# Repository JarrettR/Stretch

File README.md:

Note: Due to the constantly moving target of the KiCad file format, and also more importantly, the [new IPC plugin system](https://dev-docs.kicad.org/en/apis-and-binding/ipc-api/), this plugin hasn't been fully tested in 9, and support will be extremely limited. Some people have seen success in version 9, and I'm still happy to accept PRs, but I'm unlikely to be diving into it myself.

# Stretch

Allow your PCBs to _stretch_!

## The Process

In KiCad:

In Inkscape:

Modify:

Back to KiCad:

## Why?

This was written to address some frustrations with other "artistic" PCB workflows.
KiCad and other traditional ECAD software has poor support for curved lines, importing and processing of images/drawings, and many other features that can be expected in proper vector software.

Tools intended to bridge the gap are also lacking. [PCBmodE](https://github.com/boldport/pcbmode) is the probably the best tool out there from a pure PCB art standpoint, and it is excellent, but there is no schematic tool. And with that, no ability to handle extremely complex, functional PCBs.

KiCad has a tool to export to SVG. SVG-To-Shenzen is a tool to convert SVG files into KiCad files. Both of these are single-direction tools.

Stretch goes both ways. Much as the ideal schematic->PCB capture workflow does not exist, the PCB layout aspect must go hand-in-hand with the art aspect.

Users can start by drawing a schematic and laying out a PCB, then bring it into Inkscape to arrange a thousand LEDs into a flower arrangement, then bring it back into KiCad to lay out traces, back into Inkscape to curve the traces, back into KiCad to change their microcontroller and few pin assignments, back into Inkscape to draw out some silkscreem patterns, back into KiCad to run DRC, and so on.
The workflow is intended to be seamless and painless to go back and forth.

## Installation

- Copy this main Stretch folder into your KiCad plugin folder at `Tools->External Plugins...->Open Plugin Directory`
- Ensure the BeautifulSoup4 library is installed (e.g. run `pip install bs4` in a system command line, see Troubleshooting below for details)
- Open up a PCB and then in Pcbnew, got to `Tools->External Plugins...->Refresh Plugins`
- This has been tested on KiCad 6 and later. For a KiCad 5 legacy version, check the releases.

### Troubleshooting

If the buttons do not show up on the toolbar, the plugin may be installed but not loading successfully. The most common cause is a missing `bs4` library, which is required to run Stretch. Firstly, check to see if there are any error messages by opening up the Scripting Console from `Tools->Scripting Console` and in the "Shell" section at the top, click after the `>>>` prompt (you may have to scroll down) and type `from com_github_jarrettr_stretch import Stretch`. If you get the `>>>` prompt again without any other text, the plugin is loading correctly. Otherwise, there will be an error message: pay attention to the last line.

If it says `No module named 'bs4'`, BeatifulSoup is not installed. If you have installed it but are still getting this error, try using `pip3` instead of `pip`, or install the library with your package manager (e.g. `apt install python3-bs4`).

It's also possible to have multiple installations of Python, in which case you need to run the `pip` command from the correct installation, which can be difficult to determine. This is often the case on MacOS, where KiCad uses its own installation of Python than the system installation. To find out where the Python that KiCad is using is, go back to the `>>>` prompt above and type:
```
import sys
print(sys.base_exec_prefix)
```
This will print out a path (e.g. `/usr` or `/Applications/KiCad/KiCad.app/Contents/Frameworks/Python.framework/Versions/Current`). You should be able to add `/bin/pip` (or `pip3`) to this path and run e.g. `/Applications/KiCad/KiCad.app/Contents/Frameworks/Python.framework/Versions/Current/bin/pip3 install bs4` to install BeautifulSoup in the Python installation that KiCad is using.

After installing BeautifulSoup, use `Tools->External Plugins->Refresh Plugins` or restart KiCad to attempt re-loading Stretch. If all went well, you should have the up/down buttons on your toolbar.

If there is an error message other than missing `bs4`, try searching with the error message, and if that is inconclusive, open an issue in this repository and copy/paste the error message here.

## Workflow

- In Kicad: Open up your KiCad project, and then your PCB in Pcbnew
- Hit the "UP" arrow in your plugin bar  *(Stretch up to SVG)*
- In Inkscape: There is now a file in your PCB directory called "out.svg". Open it in Inkscape, or your preferred vector software
- Make your modifications. Bend some lines, draw some pictures, rotate some footprints
- Save your SVG
- In KiCad/Pcbnew: Hit the "DOWN" arrow  *(Stretch down to PCB)*
- Close Pcbnew and then re-open the PCB in the main KiCad window
- Continue tweaking. Change some nets, add more components
- Hit the "UP" arrow again to go right back to SVG
- In Inkscape: File->Revert to quickly reload the SVG. **Alt-F** and then **V** works as well
- Do it all again.

In Inkscape, go to `Layer->Layers...` to display a window that will allow you to show/hide/view specific PCB layers. `Edit->XML Editor...` is also a good tool to debug why something isn't working, or see what's happening under the hood. Each object has some metadata that is associated with the KiCad PCB data, so objects without this data won't work properly. It's better to copy an existing trace/zone/via/text than to try to create one from scratch.

## Limitations

Fonts will look different in your vector software than in KiCad. This includes positioning, sizing, and fonts. It will import back into the PCB editor undamaged, however.

Closing the PCB window and opening it again is annoying - There is no way to programmatically reload it from disk, as of KiCad 5. Perhaps rebuilding the existing PCB from file using the API is possible, or KiCad 6 has added some other method.

Metadata that doesn't need to be processed, or do not yet have processors written are still stored. They are unchanged and stored in the SVG so they can be imported properly back into the PCB.

Most data is processed properly! Diffs on some mildly complicated 4-layer boards are coming back clean.

This is still kind of a hack. Obviously, save and backup everything before using this, and **check your gerbers carefully** before purchasing anything. One common failure mode is that *(Stretch down to PCB)* will generate a corrupt/invalid PCB. In that case, fix the error (and report the issue), and open the backup. Clicking *(Stretch down to PCB)* will leave the backup untouched, and you can open the main file again.

I am happy to accept issues, or pull requests, and example PCBs that break the software. I may be slow to fix issues by myself, so feel free to dive in yourself!

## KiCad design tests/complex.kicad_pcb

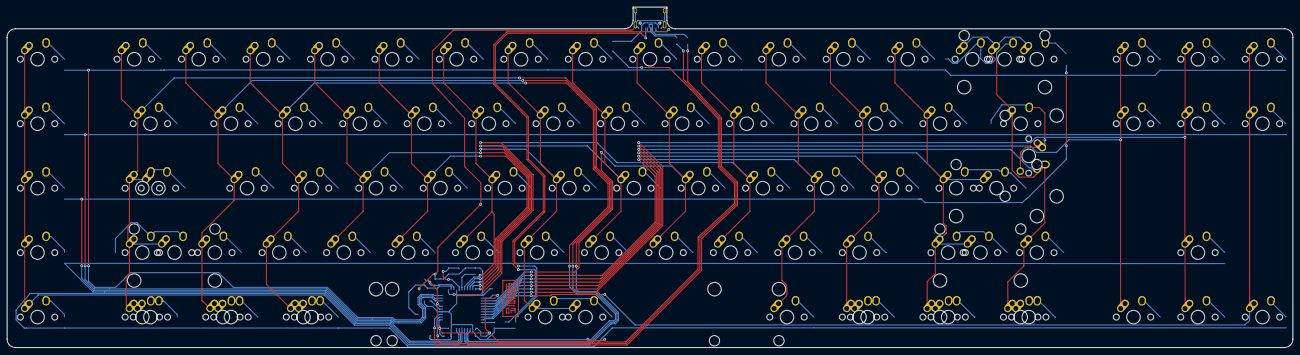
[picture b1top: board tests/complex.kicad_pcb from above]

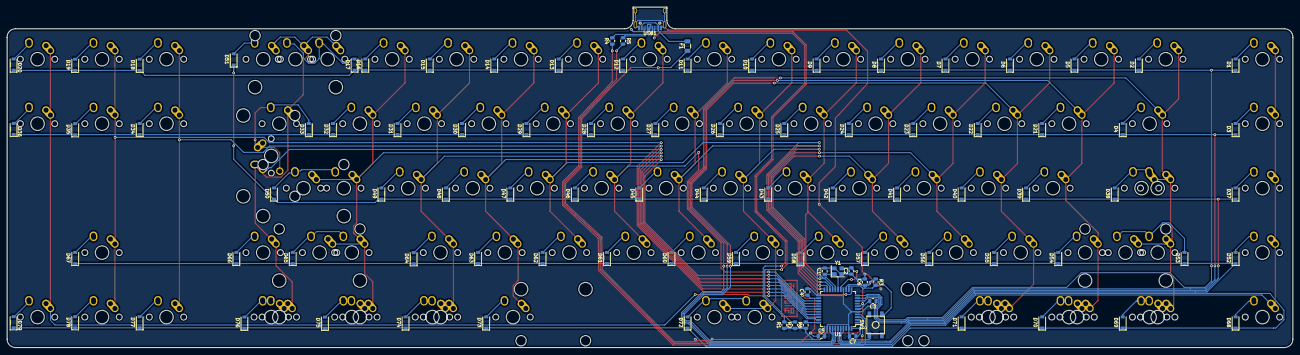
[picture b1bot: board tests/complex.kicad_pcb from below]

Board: 2 copper layers, 380.0 x 100.6 mm, 189 parts (97 on the bottom side), 116 nets.

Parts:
C1, C2: 22pF; C_0805_2012Metric
C3: 1uF; C_0805_2012Metric
C4, C5, C6: 0.1uF; C_0805_2012Metric
C7: 10uF; C_0805_2012Metric
D1, D2, D3, D4, D5, D6, D7, D8, D9, D10, D11, D12, D13, D14, D15, D16, D17, D18, D19, D20, D21, D22, D23, D24, D25, D26, D27, D28, D29, D30, D31, D32, D33, D34, D35, D36, D37, D38, D39, D40, D41, D42, D43, D44, D45, D46, D47, D48, D49, D50, D51, D52, D53, D54, D55, D56, D57, D58, D59, D60, D61, D62, D63, D64, D65, D66, D67, D68, D69, D70, D71, D72, D73, D74, D75, D76, D77, D78, D79: SOD-123; D_SOD-123
F1: 500mA; Fuse_1206_3216Metric
MX1, MX2, MX3, MX4, MX5, MX6, MX7, MX8, MX9, MX10, MX11, MX12, MX13, MX14, MX15, MX17, MX18, MX19, MX20, MX21, MX22, MX23, MX24, MX25, MX26, MX27, MX28, MX29, MX30, MX31, MX32, MX33, MX34, MX36, MX37, MX38, MX39, MX40, MX41, MX42, MX43, MX44, MX45, MX46, MX47, MX48, MX49, MX50, MX51, MX52, MX53, MX55, MX56, MX57, MX59, MX60, MX61, MX62, MX63, MX64, MX65, MX66, MX67, MX68, MX69, MX70, MX72, MX73, MX74, MX75, MX76, MX77, MX79, MX80, MX81, MX82, MX83, MX84, MX85, MX86, MX87, MX88, MX90, MX91, MX92: MX-NoLED; MX-1U-NoLED
MX16, MX54, MX58, MX71: MX-NoLED; MX-2U-NoLED
MX35: MX-NoLED; MX-ISO
MX78: MX-NoLED; MX-6.25U-ReversedStabilizers-NoLED
MX89: MX-NoLED; MX-7U-ReversedStabilizers-NoLED
R1, R2: 5.1k; R_0805_2012Metric
R3, R6: 10k; R_0805_2012Metric
R4, R5: 22; R_0805_2012Metric
SW1: SW_Push; SKQG-1155865
U1: ATmega32U4-AU; TQFP-44_10x10mm_P0.8mm
USB1: HRO-TYPE-C-31-M-12
Y1: 16MHz; Crystal_SMD_3225-4Pin_3.2x2.5mm

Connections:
+5V: C4.1, C5.1, C6.1, C7.1, F1.1, R3.1, U1.2, U1.7, U1.14, U1.24, U1.34, U1.44
COL0: MX1.1, MX20.1, MX39.1, MX56.1, MX74.1, U1.39
COL1: MX2.1, MX21.1, MX40.1, MX41.1, MX57.1, MX58.1, MX75.1, MX86.1, U1.38
COL2: MX3.1, MX22.1, MX42.1, MX59.1, MX76.1, MX87.1, U1.37
COL3: MX4.1, MX23.1, MX43.1, MX60.1, MX77.1, MX88.1, U1.36
COL4: MX5.1, MX24.1, MX44.1, MX61.1, U1.20
COL5: MX6.1, MX25.1, MX45.1, MX62.1, U1.19
COL6: MX7.1, MX26.1, MX46.1, MX63.1, U1.18
COL7: MX8.1, MX27.1, MX47.1, MX64.1, MX78.1, MX89.1, U1.21
COL8: MX9.1, MX28.1, MX48.1, MX65.1, U1.22
COL9: MX10.1, MX29.1, MX49.1, MX66.1, U1.25
COL10: MX11.1, MX30.1, MX50.1, MX67.1, U1.12
COL11: MX12.1, MX31.1, MX51.1, MX68.1, MX79.1, U1.26
COL12: MX13.1, MX32.1, MX52.1, MX69.1, MX80.1, MX90.1, U1.27
COL13: MX14.1, MX33.1, MX53.1, MX54.1, MX70.1, MX71.1, MX81.1, MX91.1, U1.28
COL14: MX15.1, MX16.1, MX34.1, MX35.1, MX55.1, MX72.1, MX82.1, MX92.1, U1.29
COL15: MX17.1, MX36.1, MX83.1, U1.30
COL16: MX18.1, MX37.1, MX73.1, MX84.1, U1.31
COL17: MX19.1, MX38.1, MX85.1, U1.32
D+: R4.2, USB1.6, USB1.8
D-: R5.1, USB1.5, USB1.7
GND: C1.2, C2.1, C3.1, C4.2, C5.2, C6.2, C7.2, R1.1, R2.1, R6.1, SW1.1, U1.5, U1.15, U1.23, U1.35, U1.43, USB1.1, USB1.12, USB1.13, Y1.2, Y1.4
unnamed: C1.1, U1.17, Y1.1
unnamed: C2.2, U1.16, Y1.3
unnamed: C3.2, U1.6
unnamed: D1.2, MX1.2
unnamed: D2.2, MX2.2
unnamed: D3.2, MX20.2
unnamed: D4.2, MX21.2
unnamed: D5.2, MX3.2
unnamed: D6.2, MX4.2
unnamed: D7.2, MX5.2
unnamed: D8.2, MX6.2
unnamed: D9.2, MX7.2
unnamed: D10.2, MX8.2
unnamed: D11.2, MX9.2
unnamed: D12.2, MX10.2
unnamed: D13.2, MX11.2
unnamed: D14.2, MX12.2
unnamed: D15.2, MX13.2
unnamed: D16.2, MX14.2
unnamed: D17.2, MX15.2, MX16.2
unnamed: D18.2, MX17.2
unnamed: D19.2, MX18.2
unnamed: D20.2, MX19.2
unnamed: D21.2, MX22.2
unnamed: D22.2, MX23.2
unnamed: D23.2, MX24.2
unnamed: D24.2, MX25.2
unnamed: D25.2, MX26.2
unnamed: D26.2, MX27.2
unnamed: D27.2, MX28.2
unnamed: D28.2, MX29.2
unnamed: D29.2, MX30.2
unnamed: D30.2, MX31.2
unnamed: D31.2, MX32.2
unnamed: D32.2, MX33.2
unnamed: D33.2, MX34.2, MX35.2
unnamed: D34.2, MX36.2
unnamed: D35.2, MX37.2
unnamed: D36.2, MX38.2
unnamed: D37.2, MX39.2
unnamed: D38.2, MX40.2, MX41.2
unnamed: D39.2, MX42.2
unnamed: D40.2, MX43.2
unnamed: D41.2, MX44.2
unnamed: D42.2, MX45.2
unnamed: D43.2, MX46.2
unnamed: D44.2, MX47.2
unnamed: D45.2, MX48.2
unnamed: D46.2, MX49.2
unnamed: D47.2, MX50.2
unnamed: D48.2, MX51.2
unnamed: D49.2, MX52.2
unnamed: D50.2, MX53.2, MX54.2
unnamed: D51.2, MX55.2
unnamed: D52.2, MX56.2
unnamed: D53.2, MX57.2, MX58.2
unnamed: D54.2, MX59.2
unnamed: D55.2, MX60.2
unnamed: D56.2, MX61.2
unnamed: D57.2, MX62.2
unnamed: D58.2, MX63.2
unnamed: D59.2, MX64.2
unnamed: D60.2, MX65.2
unnamed: D61.2, MX66.2
unnamed: D62.2, MX67.2
unnamed: D63.2, MX68.2
unnamed: D64.2, MX69.2
unnamed: D65.2, MX70.2, MX71.2
unnamed: D66.2, MX72.2
unnamed: D67.2, MX73.2
unnamed: D68.2, MX74.2
unnamed: D69.2, MX75.2, MX86.2
unnamed: D70.2, MX76.2, MX87.2
unnamed: D71.2, MX77.2, MX88.2
unnamed: D72.2, MX78.2, MX89.2
unnamed: D73.2, MX79.2
unnamed: D74.2, MX80.2, MX90.2
unnamed: D75.2, MX81.2, MX91.2
unnamed: D76.2, MX82.2, MX92.2
unnamed: D77.2, MX83.2
unnamed: D78.2, MX84.2
unnamed: D79.2, MX85.2
unnamed: R1.2, USB1.4
unnamed: R2.2, USB1.10
unnamed: R3.2, SW1.2, U1.13
unnamed: R4.1, U1.4
unnamed: R5.2, U1.3
unnamed: R6.2, U1.33
ROW0: D1.1, D2.1, D5.1, D6.1, D7.1, D8.1, D9.1, D10.1, D11.1, D12.1, D13.1, D14.1, D15.1, D16.1, D17.1, D18.1, D19.1, D20.1, U1.11
ROW1: D3.1, D4.1, D21.1, D22.1, D23.1, D24.1, D25.1, D26.1, D27.1, D28.1, D29.1, D30.1, D31.1, D32.1, D33.1, D34.1, D35.1, D36.1, U1.10
ROW2: D37.1, D38.1, D39.1, D40.1, D41.1, D42.1, D43.1, D44.1, D45.1, D46.1, D47.1, D48.1, D49.1, D50.1, D51.1, U1.9
ROW3: D52.1, D53.1, D54.1, D55.1, D56.1, D57.1, D58.1, D59.1, D60.1, D61.1, D62.1, D63.1, D64.1, D65.1, D66.1, D67.1, U1.41
ROW4: D68.1, D69.1, D70.1, D71.1, D72.1, D73.1, D74.1, D75.1, D76.1, D77.1, D78.1, D79.1, U1.40
VCC: F1.2, USB1.2, USB1.11

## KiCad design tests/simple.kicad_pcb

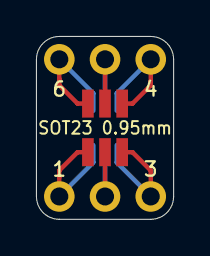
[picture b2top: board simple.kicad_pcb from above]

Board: 2 copper layers, 7.6 x 10.2 mm, 4 parts (1 on the bottom side), 6 nets.

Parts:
J1, J2: Conn_01x03; PinHeader_1x03_P2.54mm_Vertical
J3: Conn_02x03_Counter_Clockwise; SOT-23-6_Handsoldering
J4: Conn_02x03_Counter_Clockwise; SOT-363_SC-70-6_Handsoldering

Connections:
unnamed: J1.1, J3.6, J4.1
unnamed: J1.2, J3.5, J4.2
unnamed: J1.3, J3.4, J4.3
unnamed: J2.1, J3.1, J4.6
unnamed: J2.2, J3.2, J4.5
unnamed: J2.3, J3.3, J4.4

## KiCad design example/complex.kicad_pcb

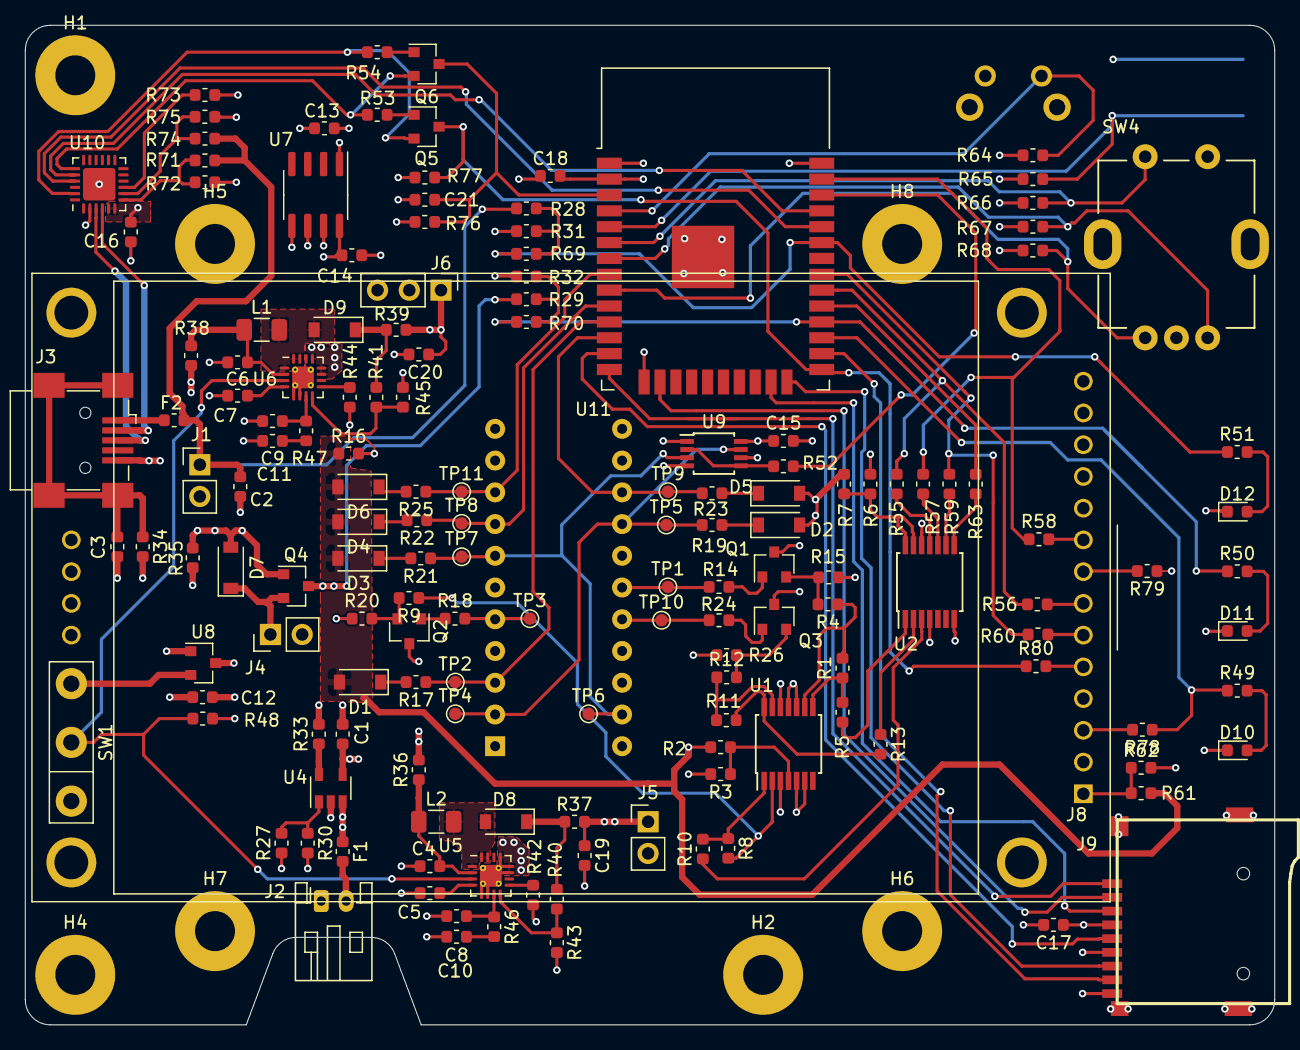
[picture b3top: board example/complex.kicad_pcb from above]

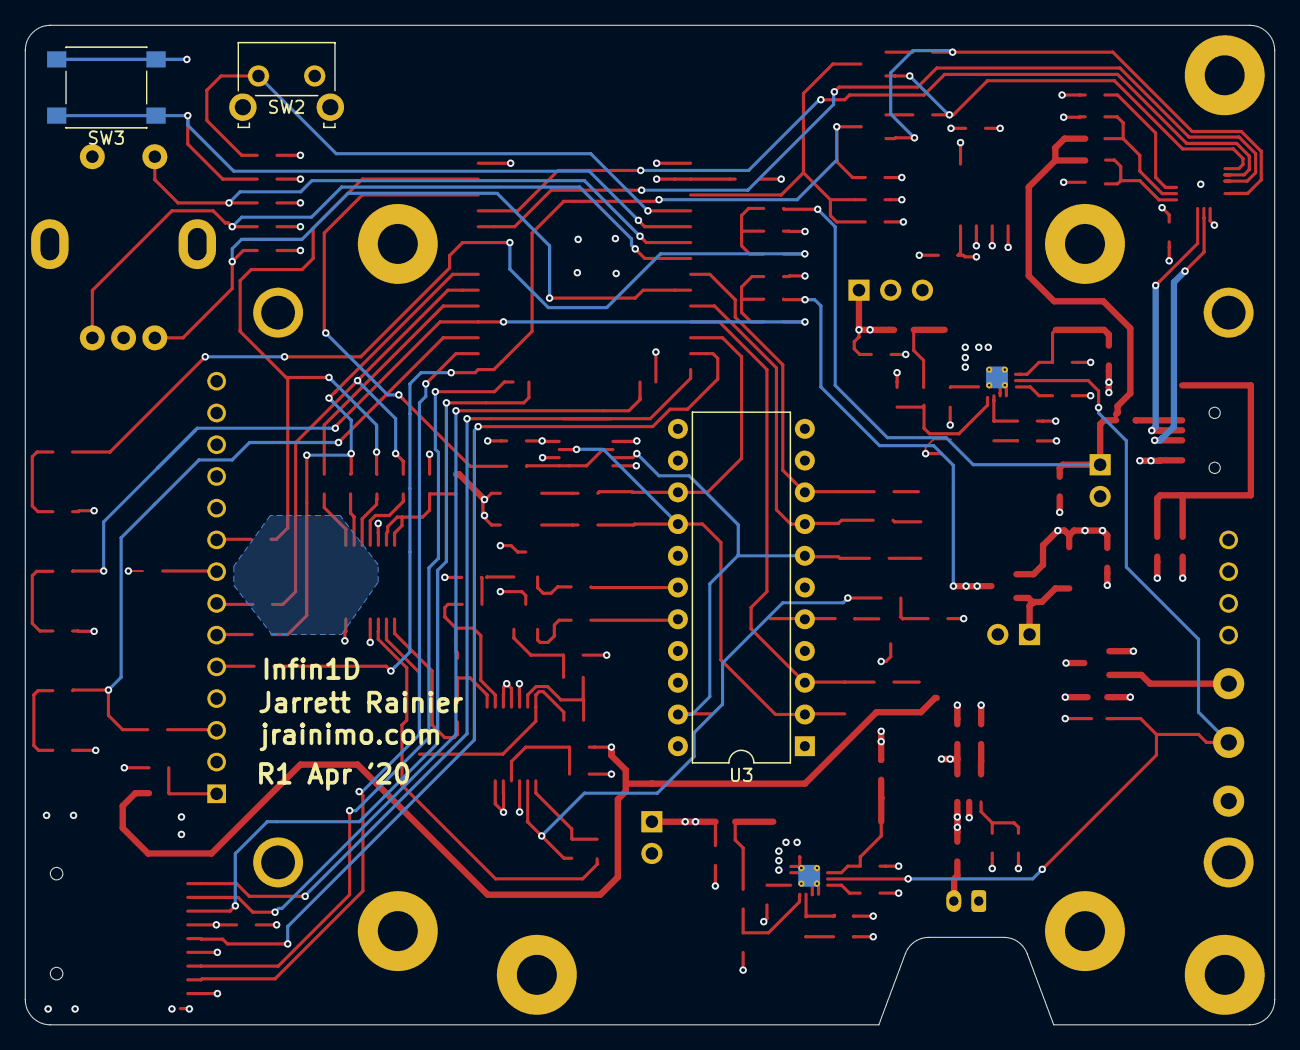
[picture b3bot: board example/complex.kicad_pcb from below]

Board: 4 copper layers, 100.0 x 80.0 mm, 165 parts (4 on the bottom side), 111 nets.

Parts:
C1, C2, C3, C4, C5, C6, C7, C8, C9, C10, C11, C12, C13, C14, C15, C16, C17, C18, C19, C20, C21: C; C_0603_1608Metric
D1, D2, D3, D4, D5, D6, D7, D8, D9: D_Schottky; D_SOD-123
D10, D11, D12: LED; LED_0603_1608Metric
F1, F2: Fuse; Fuse_0603_1608Metric
H1, H2, H4, H5, H6, H7, H8: MountingHole; MountingHole_3.2mm_M3_Pad
H3: MountingHole; logo
J1, J4, J5: Conn_01x02; PinHeader_1x02_P2.54mm_Vertical
J2: Conn_01x02; JST_PH_S2B-PH-K_1x02_P2.00mm_Horizontal
J3: USB_B_Mini; USB_Mini-B_Wuerth_65100516121_Horizontal
J6: Conn_01x03; PinHeader_1x03_P2.54mm_Vertical
J8: Conn_01x14; ILI9341-2_8
J9: Micro_SD_Card; GCT-MEM2055-00-190-01-A
L1, L2: L; L_1206_3216Metric
Q1, Q2, Q3, Q5, Q6: MMBT3904; SOT-23
Q4: DMG2301L; SOT-23
R1, R2, R3, R4, R5, R8, R9, R10, R11, R12, R13, R14, R15, R17, R18, R19, R20, R21, R22, R23, R24, R25, R26: 100; R_0603_1608Metric
R6, R16, R36, R38, R71, R74: 0; R_0603_1608Metric
R7, R61, R72, R73, R75: DNP; R_0603_1608Metric
R27, R28, R29, R30, R31, R32, R33, R34, R35, R37, R39, R40, R41, R42, R43, R44, R45, R46, R47, R48, R49, R50, R51, R52, R53, R54, R55, R56, R57, R58, R59, R60, R62, R63, R64, R65, R66, R67, R68, R69, R70, R76, R77, R78, R79, R80: R_US; R_0603_1608Metric
SW1: SW_SPDT; SIP-3
SW2: -; SW_Tactile_SKHH_Angled
SW3: SW_Push; SW_Push_1P1T_NO_6x6mm_H9.5mm
SW4: Rotary_Encoder_Switch; PEC11R
TP1, TP2, TP3, TP4, TP5, TP6, TP7, TP8, TP9, TP10, TP11: TestPoint; TestPoint_Pad_D1.0mm
U1: LM2902; TSSOP-14_4.4x5mm_P0.65mm
U2: MCP3004; TSSOP-14_4.4x5mm_P0.65mm
U3: ILX555K; DIP-22_W10.16mm
U4: MCP73831-2-OT; SOT-23-5
U5, U6: TPS55340RTE; WQFN-16-1EP_3x3mm_P0.5mm_EP1.75x1.75mm_ThermalVias
U7: AP2115M; SOIC-8_3.9x4.9mm_P1.27mm
U8: MAX809; SOT-23
U9: 74LVC2G86; TSSOP-8_3x3mm_P0.65mm
U10: CP2104; QFN-24-1EP_4x4mm_P0.5mm_EP2.6x2.6mm
U11: ESP32-WROOM-32D; ESP32-WROOM-32

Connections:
+3V3: C13.1, C15.1, C16.1, C17.1, C18.1, J6.3, J8.4, J9.4, R6.2, R62.1, R64.2, R65.2, R66.2, R67.2, R68.2, R72.2, R73.2, R76.2, R77.2, R79.1, U7.1, U9.1, U9.8, U10.5, U10.6, U11.2
+5V: C14.1, C20.1, D1.2, D2.2, D3.2, D4.2, D5.2, D6.2, J6.1, R2.2, R7.2, R16.1, R16.2, R39.1, R61.1, U7.5, U7.8
+12V: C19.1, J5.1, Q1.3, Q2.3, Q3.3, R3.2, R37.1, U3.6
+BATT: C12.1, F1.1, Q4.3, R29.1, U4.3, U8.3
/p1-power/BATMON: R29.2, R32.1, R70.2
/p1-power/BUSMON: R28.2, R31.1, R69.2
/p1-power/D+: J3.3, U10.3
/p1-power/D-: J3.2, U10.4
/p1-power/PWR_EN: R48.1, SW1.2, U5.3, U6.3
/p2-micro/ADC_CLK: R55.2, U2.11
/p2-micro/ADC_CS: R63.2, U2.8
/p2-micro/ADC_MISO: R57.2, U2.10
/p2-micro/ADC_MOSI: R59.2, U2.9
/p2-micro/CLK: R55.1, R56.1, U11.30
/p2-micro/DTR: Q5.2, R54.2, U10.23
/p2-micro/ENC_A: R68.1, SW4.A, U11.9
/p2-micro/ENC_B: R67.1, SW4.B, U11.7
/p2-micro/ENC_SW: R66.1, SW4.S1, U11.6
/p2-micro/ESP_RST: C21.1, Q6.3, R76.1, U11.3
/p2-micro/GPIO0: Q5.3, R77.1, R80.1, U11.25
/p2-micro/LED1: R49.1, R78.1, U11.27
/p2-micro/LED2: R50.1, R70.1, U11.28
/p2-micro/LED3: R51.1, R69.1, U11.33
/p2-micro/MISO: R59.1, R60.1, U11.31
/p2-micro/MOSI: R57.1, R58.1, U11.37
/p2-micro/ROG-B: R25.1, TP11.1, U3.9, U11.8
/p2-micro/ROG-G: R23.1, TP9.1, U3.14, U11.12
/p2-micro/ROG-R: R22.1, TP8.1, U3.8, U11.10
/p2-micro/RS: R17.1, TP2.1, U3.3, U11.11
/p2-micro/RTS: Q6.2, R53.2, U10.19
/p2-micro/RXD: U10.21, U11.34
/p2-micro/SD_CLK: J9.5, U11.13
/p2-micro/SD_CMD: J9.3, U11.23
/p2-micro/SD_DATA0: J9.7, U11.24
/p2-micro/SD_DATA1: J9.8, U11.26
/p2-micro/SD_DATA2: J9.1, U11.14
/p2-micro/SD_DATA3: J9.2, U11.16
/p2-micro/SW1: R64.1, SW2.1, U11.4
/p2-micro/SW2: R65.1, SW3.1, U11.5
/p2-micro/TFT_CS: J8.3, R78.2
/p2-micro/TFT_DC: J8.5, R80.2
/p2-micro/TFT_LED: J8.8, R79.2
/p2-micro/TFT_MISO: J8.9, R58.2
/p2-micro/TFT_MOSI: J8.6, R60.2
/p2-micro/TFT_SCK: J8.7, R56.2
/p2-micro/TH: R52.1, U11.36
/p2-micro/TH1: R19.1, TP4.1, TP5.1, U3.2, U3.15, U9.7
/p2-micro/TH2: R21.1, TP6.1, TP7.1, U3.7, U3.21, U9.3
/p2-micro/TXD: U10.20, U11.35
/p3-sensor/VOUT-B: Q3.2, R12.2, R26.2
/p3-sensor/VOUT-G: Q2.2, R9.2, R20.2
/p3-sensor/VOUT-R: Q1.2, R4.2, R15.2
GND: C1.2, C2.2, C3.2, C4.2, C5.2, C6.2, C7.2, C8.2, C9.2, C10.2, C11.2, C12.2, C13.2, C14.2, C15.2, C16.2, C17.2, C18.2, C19.2, C20.2, C21.2, D10.1, D11.1, D12.1, J1.2, J2.1, J3.5, J4.2, J5.2, J6.2, J8.2, J9.6, J9.9, R15.1, R20.1, R26.1, R30.2, R31.2, R32.2, R33.2, R34.2, R35.2, R42.2, R43.2, R44.2, R45.2, R48.2, R75.1, SW2.2, SW3.2, SW4.C, SW4.S2, U1.3, U1.5, U1.6, U1.10, U1.11, U1.12, U2.4, U2.7, U2.12, U3.1, U3.4, U3.10, U3.11, U3.12, U3.13, U3.16, U3.19, U3.20, U3.22, U4.2, U5.5, U5.6, U5.11, U5.12, U5.13, U5.17, U6.5, U6.6, U6.11, U6.12, U6.13, U6.17, U7.6, U7.7, U8.1, U9.4, U9.6, U10.2, U10.25, U11.1, U11.15, U11.38, U11.39
unnamed: C3.1, J3.6, R34.1
unnamed: C4.1, L2.1, R36.1, U5.2
unnamed: C5.1, U5.4
unnamed: C6.1, L1.1, R38.1, U6.2
unnamed: C7.1, U6.4
unnamed: C8.1, R46.1, U5.7
unnamed: C9.1, R47.1, U6.7
unnamed: C10.1, R46.2
unnamed: C11.1, R47.2
unnamed: D1.1, R17.2
unnamed: D2.1, R19.2
unnamed: D3.1, R21.2
unnamed: D4.1, R22.2
unnamed: D5.1, R23.2
unnamed: D6.1, R25.2
unnamed: D8.1, R37.2, R40.1
unnamed: D8.2, L2.2, U5.1, U5.15, U5.16
unnamed: D9.1, R39.2, R41.1
unnamed: D9.2, L1.2, U6.1, U6.15, U6.16
unnamed: D10.2, R49.2
unnamed: D11.2, R50.2
unnamed: D12.2, R51.2
unnamed: F1.2, J2.2
unnamed: F2.2, J3.1
unnamed: J8.1, R61.2, R62.2
unnamed: Q1.1, R14.1
unnamed: Q2.1, R18.1
unnamed: Q3.1, R24.1
unnamed: Q5.1, R53.1
unnamed: Q6.1, R54.1
unnamed: R1.1, R5.2, U1.8
unnamed: R1.2, R4.1, U1.9
unnamed: R2.1, R3.1, U1.4
unnamed: R5.1, U2.1
unnamed: R6.1, R7.1, U2.13, U2.14
unnamed: R8.2, R9.1, U1.2
unnamed: R10.1, U2.3
unnamed: R8.1, R10.2, U1.1
unnamed: R11.1, R13.2, U1.14
unnamed: R11.2, R12.1, U1.13
unnamed: R13.1, U2.2
unnamed: R14.2, TP1.1, U3.17
unnamed: R18.2, TP3.1, U3.5
unnamed: R24.2, TP10.1, U3.18
unnamed: R27.2, R30.1, U4.1
unnamed: R33.1, U4.5
unnamed: R40.2, R43.1, U5.8
unnamed: R41.2, R45.1, U6.8
unnamed: R42.1, U5.9
unnamed: R44.1, U6.9
unnamed: R52.2, U9.2, U9.5
unnamed: R63.1, U11.29
unnamed: R71.1, R72.1, U10.7
unnamed: R73.1, U10.9
unnamed: R74.1, R75.2, U10.8
unnamed: SW1.3, U8.2
VBUS: C1.1, C2.1, D7.2, F2.1, J1.1, Q4.1, R27.1, R28.1, R35.1, R71.2, R74.2, U4.4
VIN: D7.1, J4.1, Q4.2, R36.2, R38.2

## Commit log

2020-05-03 Successfully converting PCB segments to SVG
2020-05-03 Layers to SVG
2020-05-03 Unknown fields handled as unprocessed metadata
2020-05-03 Made parsers consistent output
2020-05-03 SVGs fully generated, with traces assigned to layers
2020-05-03 More accurate filename
2020-05-03 gr_lines SVG parser done
2020-05-03 via SVG parser done
2020-05-03 Modules roughly parsing
2020-05-03 Grouping modules properly
2020-05-03 Fixed all offset/rotation errors encountered so far
2020-05-03 Added quick docs
2020-05-04 Load PCB -> Save PCB pipeline works
2020-05-04 Initial SVG->PCB chain
2020-05-04 Segments and layers parsing to PCB
2020-05-04 gr_lines done
2020-05-04 modules mostly done
2020-05-04 More complicated modules mostly done
2020-05-04 Square pads working
2020-05-04 Fixed up pads
2020-05-04 Go away, bezier warning
2020-05-04 One case of svg arcs generating
2020-05-05 Arcs
2020-05-05 Python 2 compatibility hacks (ugh)
2020-05-05 Double plugin install hack
2020-05-05 Renamed svg_parse to pcb_write, seems clearer
2020-05-06 Arc positioning
2020-05-06 Arc angles
2020-05-06 Unhardcoded filenames
2020-05-06 Plugin fixes and arc calc error workaround
2020-05-06 Fixed module duplication
2020-05-07 Updated docs
2020-05-07 Doc corrections
2020-05-07 Added beautifulsoup standalone
2020-05-31 Disable internal BS4 module, for now
2020-05-31 Fixed SVG layer ordering
2020-05-31 Fixed via appearance in SVG
2020-05-31 Fixed via layer ordering
2020-05-31 Additional tstamp / tedit tags in modules
2020-06-01 Initial text parsing
2020-07-17 hack / fixed erroneous spaces added to text fields
2020-07-17 Bezier curve to SVG support
2020-07-18 Text mirroring
2020-07-18 Centre align text
2020-07-18 Implemented zones to SVG
2020-07-19 Bezier curves in PCBs done, zones in progress
2020-07-21 PCB zone parsing done
2020-07-22 Fixed relative positioning issue on gr_curve
2020-07-22 Polygon to svg conversion
2020-07-24 Text and polygon PCB writing initial
2020-07-25 Text decoding
2020-07-25 Bunch of fixes to reduce diffs in input vs output
2020-07-27 Module text parsing
2020-07-27 CLeaning up more diffs
2020-08-03 Renamed plugin
2020-08-03 Fixed up old name
2020-08-03 Mitigated errors found in another PCB
2020-08-04 Fixed relative import
2020-08-06 Fixed directory paths on Linux
2020-08-06 Relative imports for KiCad only
2020-08-07 More relative import fixes
2020-08-07 Last one?
2020-09-17 Fixed pad rotation within modules in SVG
2020-09-23 Revamped via parsing to new method and added blind via detection
2020-12-29 Improved docs
2020-12-31 Initially split up board elements
2020-12-31 Updated beautifulsoup
2020-12-31 Started figuring out object formats
2021-01-01 Handle problems SVGs a little better
2021-01-07 Cleaned up general structure for via
2021-01-07 Listed board-level components
2021-01-08 Roughed in segments
2021-01-09 Python imports
2021-01-09 Initially running
2021-01-10 Layer and segment conversion to SVG working
2021-01-10 Via to SVG working
2021-01-10 gr_line to SVG working
2021-01-11 gr_arcs to SVG working
2021-01-11 gr_circle to SVG working
2021-01-11 Added layer / colour tools
2021-01-11 module incomplete but working so far
2021-01-14 Pad to SVG roughly done
2021-01-14 Fixed pad rotations
2021-01-14 Polys, zones, curves, and metadata
2021-01-16 Fixed up zones
2021-09-18 Fix KiCad's broken relative import garbage
2021-09-18 Added PCB conversion methods
2021-09-18 Roundtrip for layers section working
2021-09-19 Mostly worked on metadata
2021-09-23 Metadata from and to SVG working better
2021-09-23 Round trip working! Among supported object types
2021-09-30 Progress on text conversion
2021-10-04 Removed more errors
2021-10-05 Module more fleshed out
2021-10-09 polys in modules
2021-10-10 Text roundtrip, not quite complete yet
2021-10-13 Poly working in module
2021-10-13 Arcs somewhat working
2021-10-14 Diff reductions
2021-10-16 pad MVP
2021-10-20 Added some missing fields
2021-10-20 Remove old Via code
2021-10-22 Fixed module pad rotation
2021-10-23 Text rotation (still not good), and module models
2021-10-26 Maybe slightly better on diffs
2021-10-30 Text able to use transforms
2021-11-14 Roundrect padtype and text in modules following hidden layers
2021-11-14 Blind / micro vias no longer breaking
2021-11-14 Simplified arc calculation, also fixing problems with edge cases
2021-11-14 Removed unused function
2021-11-14 Added Zone SVG handling
2021-11-15 Removed zone duplicaton
2021-11-15 Added oval pad handling
2021-12-18 Text round trip works
2021-12-18 Curve to PCB using old dirty hack
2022-01-01 Fixed KiCad plugin integration
2022-01-05 Removed old plugin action file
2022-01-05 Fixed divide by zero
2022-01-05 Windows import fixes
2022-01-05 Various Windows (py27) fixes)
2022-01-05 Adding back in to_pcb and repaired it
2022-01-06 tabs, spaces
2022-01-06 Python 3 doesn't have a unicode type
2022-01-06 Fixed pad in module rotation for weird angles
2022-01-06 SVG template no longer growing with multiple stretch-to-svg presses
2022-01-07 Text translation has a default Y value
2022-01-12 Colour() fixes
2022-01-12 Fixed layer parameter ordering
2022-01-13 Some changes that will make kicad 6 support easier
2022-01-13 Fixed modules accidentally being skipped
2022-01-13 Added circle support outside of pads
2022-07-16 Added islands to zones
2022-07-16 Added stdout redirect and made kicad 6 zones to SVG work
2022-07-16 Reduced zone line width
2022-07-16 Layers and arcs working
2022-07-16 Polys working back to PCB
2022-07-16 Zones generating all layers now
2022-07-17 Module properties working on 6
2022-07-17 Pintype and pinfunction added
2022-07-17 Added current state to readme
2022-07-18 Fixed zones with only one layer
2022-07-18 Arcs fixed for small sweep lengths
2022-07-18 Large sweeps as well
2022-07-19 Nonzero rotation axis in transforms are calculated properly
2022-07-24 Initial py3 addition of BS4
2022-07-24 Relative import fixes
2022-07-26 Seems to work
2022-09-03 Added initial BS for Py2
2022-09-03 Fixed Py2 relative imports for BS3
2022-09-03 Changed over plugin imports
2022-09-06 Unfilled zone bug
2022-09-12 Docs changed and added logging for segments
2022-09-14 Add macOS dependency installation instruction
    Took me a while to figure it out
2022-10-15 Added backup strategy
2022-10-25 Fixed text index error
2022-10-31 Support for ovals with only R terms instead of RX and RY
2022-10-31 Added initial PCM stuff
2022-10-31 PCM tweaks for this system
2022-11-01 Added logo
2022-11-09 Documentation tweaks
2022-11-09 Changed PCM resource image name
2022-11-09 Grammar fix
2022-12-12 Fixed typo
2022-12-12 Mitigated issue with variable lengths in the AT field of text
2023-02-14 Fixed Python type issues
2023-03-28 Removed Py2 stuff and switched over to kibs4 folder
2023-03-28 Added kibs4
2024-03-14 Cast string in poly.py
2024-03-15 Removed internal BS4 instance, it was too much of a headache
2024-03-15 Fixes #34
2024-03-15 Fixes #21
2024-04-05 Fixed error when 3D model is hidden
2024-05-02 Removed unnecessary imports that happen too early. Mitigates #36
2025-04-25 Add troubleshooting about bs4 dep to README
    It is not mentioned anywhere that this requires bs4, and if people don't have it installed it just fails silently. Add some instructions to help troubleshoot this.
2025-04-25 Add note about scrolling
    Often there's initialization stuff
2025-04-25 Add note about Refresh Plugins
2025-06-06 Clarifying current status
